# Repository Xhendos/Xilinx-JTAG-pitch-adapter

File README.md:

# Xilinx JTAG pitch adapter

Quite a lot of Xilinx SoCs use a 14 pin JTAG connection in order to program the target device.
However, the pitch can vary. For instance, the JTAG-HS3 developed by Digilent has 2.0mm pitch between each adjacent pin
whereas the MYIR-Zturn board containing the Xilinx Zynq 7020 SoC has a 14 pin 2.54mm pitch JTAG connector.
This is visually shown in the two images down below as well. Keep in mind that these images are not scaled.

This repository tries to solve this issue by hosting the design files and documentation of a passive connector
that converts the 2.0mm pitch 14 pin connector to a 2.54mm pitch 14 pin connector.

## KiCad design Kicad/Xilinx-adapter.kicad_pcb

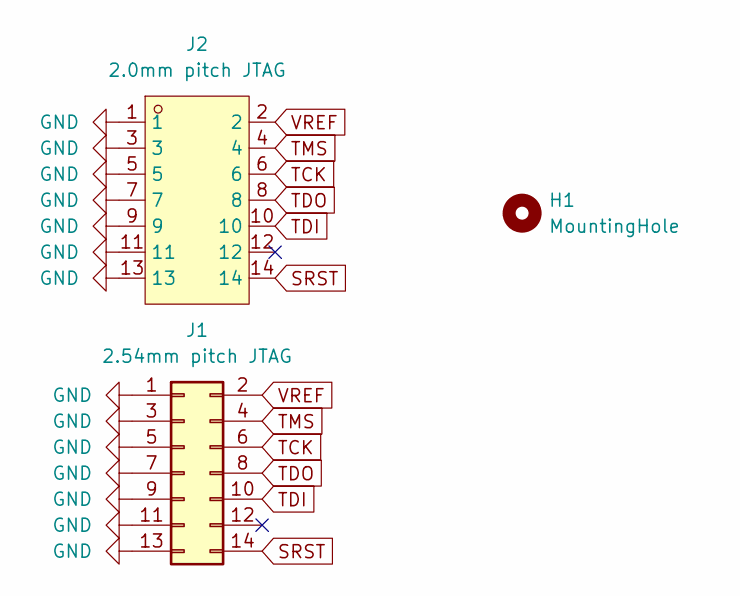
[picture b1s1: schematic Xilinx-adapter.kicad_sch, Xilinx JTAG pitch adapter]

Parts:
H1: MountingHole; MountingHole_2.2mm_M2
J1: 2.54mm pitch JTAG; PinHeader_2x07_P2.54mm_Vertical
J2: 2.0mm pitch JTAG; CONN-TH_14P-P2.00-V-M_1-1734493-4; LCSC Part C404217

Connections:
GND: J1.1, J1.3, J1.5, J1.7, J1.9, J1.11, J1.13, J2.1, J2.3, J2.5, J2.7, J2.9, J2.11, J2.13
SRST: J1.14, J2.14
TCK: J1.6, J2.6
TDI: J1.10, J2.10
TDO: J1.8, J2.8
TMS: J1.4, J2.4
VREF: J1.2, J2.2

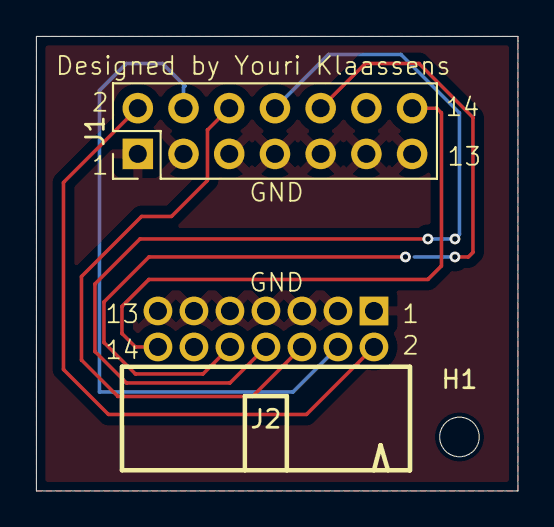
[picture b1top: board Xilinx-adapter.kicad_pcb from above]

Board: 2 copper layers, 26.8 x 25.2 mm, 3 parts (0 on the bottom side), 7 nets.

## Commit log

2025-04-06 added figures
2025-04-06 Design added
